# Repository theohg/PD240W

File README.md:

# PD240W

An adjustable power supply for motor drives using USB-C Power Delivery negotiation, supporting up to **240W at 48V 5A**. This device is designed to be compatible with USB-PD up to 3.2. Firmware runs on a Raspberry Pi Pico ([RP2040](https://www.raspberrypi.com/products/rp2040/)).

Follow the latest project logs and updates on <a href="https://hackaday.io/project/205084-pd240w" target="_blank" title="PD240W on Hackaday.io">
Hackaday.io 
</a>

> [!WARNING]
> **Disclaimer**: Firmware v2.0.0 includes guarded AVS/EPR negotiation, startup restore, and EPR-exit handling, but high-voltage charger interoperability still depends on the source and cable combination you test with. Validate 28V/36V/48V operation on your hardware.

## Table of Contents

- [Features](#features)
- [Hardware](#hardware)
- [Quick Start](#quick-start)
- [Controls](#controls)
- [Firmware Structure](#firmware-structure)
- [Want one?](#want-one)
- [Planned Features](#planned-features)
- [Acknowledgements](#acknowledgements)

## Features

- **USB-C Power Delivery**: Negotiates Fixed, PPS (3.3-21V programmable), and AVS (15-48V EPR) profiles
- **Current Limiting**: Adjustable 10mA-5A via INA228 power monitor with hardware overcurrent protection
- **LCD Interface**: 240x320 ST7789 display with anti-aliased fonts and Prusa-style encoder navigation
- **Safety**: Overcurrent ISR, overtemperature monitoring (NTC + INA228)
- **Settings Persistence**: User settings stored in RP2040 flash with CRC32 validation
- **Auto PPS/AVS Tuning**: Closed-loop voltage correction for PPS/AVS charger output accuracy
- **Charger Diagnostics**: On-device PD revision, charger identity, cable inference, and max-power reporting
- **Remote CLI**: USB serial command interface for measurements, PD selection, and settings updates
- **Energy Monitoring**: Tracks mAh delivered since boot via INA228 charge accumulator
- **17V Buck Output**: Optional mock STO/SBC voltage for motor drive safety circuits
- **Configurable**: Brightness, auto-dim, startup melody, auto-output on boot and more

## Hardware

| Type | Path | Contents |
|------|------|----------|
| PCB (STEP) | `3D_models/PD240W_PCB.stp` | Full PCB 3D model |
| Enclosure (STL) | `3D_models/enclosure/` | Casing top/bottom, knob, button, LCD support, SWD cover |
| Gerbers | `PCB_files/Manufacturing/Fabrication/` | PCB manufacturing files |
| BOM | `PCB_files/Manufacturing/Assembly/` | Bill of materials |
| Pick & Place | `PCB_files/Manufacturing/Assembly/` | Pick and place file |

### Hardware Erata

USB data lines (D+/D-) are reversed in the current PCB revision, preventing native USB communication between the RP2040 and the USB host. This can be easily fixed by crossing the D+ and D- lines on the PCB by crossing the series 27Ω resistors as shown below:

## Quick Start

### Flash Pre-built Firmware

1. Download `PD240W.uf2` from the [latest release](https://github.com/theohg/PD240W/releases/latest)
2. Hold **BOOTSEL** button on the Pico while connecting USB
3. Drag `PD240W.uf2` to the mounted `RPI-RP2` drive

### Build from Source

Requires: [Pico SDK 2.3.0](https://github.com/raspberrypi/pico-sdk), ARM GCC toolchain, CMake, Ninja

```bash
git clone --recurse-submodules https://github.com/theohg/PD240W.git
cd PD240W

mkdir -p build && cd build
cmake -G Ninja ..
ninja
```

The output binary is `build/PD240W.uf2`.

The INA228 driver is tracked as a Git submodule in `external/ina228_multiplatform`. If you already cloned the repository without submodules, run:

```bash
git submodule update --init --recursive
```

PD240W does not automatically follow the newest INA228 library release. The version is pinned by the parent repository's recorded submodule commit for `external/ina228_multiplatform`, and that exact checked-out commit is what gets compiled into the firmware. Prebuilt `PD240W.uf2` releases already include that pinned INA version.

### Flash via SWD

```bash
openocd -f interface/cmsis-dap.cfg -f target/rp2040.cfg \
  -c "adapter speed 5000; program build/PD240W.elf verify reset exit"
```

> [!IMPORTANT]
> **EEPROM Initial Setup**: Before full PD negotiation can work, you must flash the **TPS26750 EEPROM** configuration. This is done via the **EEPROM Flash** workflow found in the **Settings** menu. 
> 
> **Note**: Before the EEPROM is flashed, the board will only power on when connected to a standard 5V non-PD charger (USB BC1.2 mode).

Once the firmware has been successfully flashed, connect the device to a compatible USB-PD power source and interact with the encoder and buttons to navigate the menus and adjust settings as explained below.

> [!NOTE]
> Finding a compact and affordable charger supporting **USB-PD 3.1** (up to 48V EPR) is currently quite rare. Here are a few known options:
>
> | Model | Max single-port PD Output | Voltage Profile | Approx. Price |
> |---|---|---|---|
> | **[UGREEN Nexode 140W](https://fr.ugreen.com/products/ugreen-nexode-140w-chargeur-usb-c-pd-3-1-3-ports)** | 140W | 28V @ 5A | ~60€ |
> | **[Framework Power Adapter - 180W](https://frame.work/fr/fr/products/16-power-adapter?v=FRANCR000F)** | 180W | 36V @ 5A | ~109€ |
> | **[HKY 240W GaN Charger](https://www.amazon.de/-/en/Charger-Framework-Thunderbolt-External-ADP-240KB/dp/B0FLXY1HYW/ref=sr_1_2?crid=3N3IPHZQ5LLC7&dib=eyJ2IjoiMSJ9.Hby-yLg1Ti0JNivqvDzvN57zIH6zG4_c9wlyL50Z52GmOPyP_vKubcMJ3zNZ7RRcIgOo2FKgZio1hprqALfRdOTl2DQ7Dp27o4l66qmaDQw9ctSuX0EaWnDfyVwVAMaSwnUP7h1NBuraYlZnAgiljw.9cbe3P4mLf8D7-0faSCcJpKki5cfrjZLwFO-zW9XlJw&dib_tag=se&keywords=hky+240w&qid=1769454134&sprefix=hky+240w%2Caps%2C102&sr=8-2)** | 240W | 48V @ 5A | ~90€ |
> | **[Framework Power Adapter - 240W](https://frame.work/fr/fr/products/power-adapter-240w?v=FRAKMX000F)** | 240W | 48V @ 5A | ~120€ |
> | **[UGREEN NEXODE 500W](https://eu.ugreen.com/products/ugreen-nexode-500w-6-port-gan-desktop-fast-charger)** | 240W | 48V @ 5A | ~250€ |

## Controls

| Input | Action |
|-------|--------|
| Encoder Rotate | Navigate menus / Adjust values |
| Encoder Click | Confirm / Select |
| BTN1 (top) | Toggle load switch output |
| BTN2 (bottom) | Toggle 17V buck (requires VBUS > 18V) |

### Menu Structure

```mermaid
graph TD
  %% Nodes
      Boot([Boot]) -->|≤2s| Main[Main Screen]
      Main -->|Error| Fault[Fault Screen]
      Fault -->|Click| Main
      
      Main <-->|Click| Menu[Main Menu]

      Menu --> Voltage[Select Voltage]
      Menu --> Current[Current Limit]
      Menu --> Settings[Settings]
      Menu --> AboutFirmware[About PD240W]
      Menu --> AboutCharger[About This Charger]
      Menu --> Back[Back]

      Voltage <-->|Select PDO| AdjV[Adjust Voltage]
      Current <-->|Set Limit| AdjC[Adjust Current]
      
      Settings --> EEPROM[Flash EEPROM]
      Settings --> Configs[Params: Brightness / Sounds / Tuning...]
      AboutFirmware --> Main
      AboutCharger --> Main
      
      %% Styling
      classDef default fill:#f9f9f9,stroke:#333,stroke-width:1px;
      classDef alert fill:#ffcccc,stroke:#cc0000,stroke-width:2px;
      class Fault alert;
```

| Menu Item | Description |
|-----------|-------------|
| Select Voltage | Fixed / PPS / AVS PDO selection |
| Current Limit | 10mA - 5A output current limit adjustment with encoder acceleration |
| Settings | EEPROM flash workflow plus tuning, startup, brightness, and sound options |
| About PD240W | Device identity, firmware build info, flash usage, and project link |
| About This Charger | Live PD revision, CC orientation, QC inference, and cable diagnostics |
| Back | Return to the main live display |

## Firmware Structure

```
src/
├── main.cpp                        Entry point, non-blocking main event loop
├── hardware.h/cpp                  Hardware singleton aggregating all drivers
├── interrupts.h/cpp                Centralized GPIO interrupt router (RP2040 single-callback)
│
├── config/
│   ├── board_config.h              Pin definitions (Board:: namespace)
│   ├── app_config.h                Timeouts, thresholds, limits (AppConfig:: namespace)
│   └── version.h                   Firmware & hardware version, author...
│
├── drivers/                        Low-level hardware drivers (no business logic)
│   ├── display/
│   │   ├── st7789.h/cpp            SPI LCD driver with AA font rendering
│   │   ├── aa_font.h               Anti-aliased font data structure
│   │   └── font_inter_*.h          Generated Inter font bitmaps (14/20/28px)
│   ├── power/
│   │   └── tps26750/               USB-PD controller: PDO discovery, contract negotiation
│   ├── input/
│   │   ├── rotary_enc.h/cpp        Quadrature encoder with velocity tracking
│   │   ├── button.h/cpp            Debounced button with click/long-press
│   │   └── adc_inputs.h/cpp        VBUS voltage + NTC temperature (ADC channels)
│   ├── gpio/                       SimpleIO: digital output with non-blocking blink
│   ├── buzzer/                     PWM buzzer with melody playback
│   └── rgb_led/                    SK6812 via PIO state machine
│
├── logic/                          Application logic
│   ├── state_machine.h/cpp         BOOT -> MAIN <-> MENU <-> ADJUST, FAULT handling
│   ├── safety.h/cpp                Temperature/voltage/current monitoring, fault triggers
│   ├── pd_manager.h/cpp            PD contract caching, PPS keep-alive, auto-tuning
│   ├── settings.h/cpp              Flash persistence with CRC32, debounced saves
│   └── tps_eeprom_workflow.h/cpp   TPS26750 EEPROM compare/flash state machine
│
├── ui/
│   ├── display_manager.h/cpp       All screen rendering (boot, main, menu, adjust, fault)
│   ├── font_config.h               Central font size mapping (FONT_LARGE/MEDIUM/SMALL)
│   └── assets/synapticon_logo.h    Boot screen logo bitmap
│
├── utils/
│   ├── logging.h                   LOG_INFO/WARN/ERROR/DEBUG/CRITICAL macros
│   ├── pd_voltage.h                Shared programmable-voltage alignment helper
│   ├── tps_eeprom_loader.h/cpp     Low-level TPS26750 EEPROM read/write
│   └── tps26750_patch.c            TPS26750 binary configuration blob
```

## Want one?

Feel free to order assembled PCBs, flash the firmware, and test it for yourself! Manufacturing 5 assembled PCBs will cost approximately **$415**. 

The project is open for contributions. Don't hesitate to improve the code, report bugs, or suggest new features via Pull Requests and Issues!

## License and Copyright

This repository contains different types of source files, which are licensed as follows:

### 1. Hardware files (CC BY-NC 4.0)
All hardware design files in the PCB_files directory (Schematics, PCB layout, Gerbers, BOM) and 3D printable enclosure files are licensed under the **Creative Commons Attribution-NonCommercial 4.0 International License**. 

You are free to download, modify, and build this board for personal, educational, and hobbyist use. However, you may **not** use these designs for commercial purposes (such as manufacturing and selling the boards) without prior written permission.

Please see the [LICENSE.txt](./LICENSE.txt) file for full terms.

### 2. Firmware & Software (MIT License)
The firmware and software source code in this repository is licensed under the **MIT License**. 

You are free to use, modify, and distribute the software component of this project. 

Please see the [LICENSE-FIRMWARE.txt](./LICENSE-FIRMWARE.txt) file for full terms.

## Planned Features for V2.1.0+

- **PPS battery charging in Constant Current (CC) mode**: PPS allows a fixed current mode that can be used for battery charging. This is to be tested by charging lithium-ion battery packs.
- **Improved CLI interface**: Needs more testing and polish.
- **Extended PPS and AVS Range**: Support for PPS voltages as low as 3.5V, AND SPR AVS profiles down to 9V.

## Acknowledgements

This project was made possible by [Synapticon GmbH](https://www.synapticon.com), who funded and supported its development. Thank you for providing the resources, hardware, and opportunity to bring PD240W to life.

Inspiration for this project was taken from the great work on portable USB-C PD power supplies by CentyLab on the [PocketPD](https://hackaday.io/project/194295-pocketpd-usb-c-portable-bench-power-supply) project and Alex Xia with his [ProtoV MINI](https://hackaday.io/project/204461-protov-mini-tiny-usb-c-breadboard-power-supply).

All work done on this project, from Hardware design to Firmware development, was done by me, as the sole contributor. I am grateful for the support and feedback from the community, and I hope this project can be a useful resource for anyone interested in USB-C PD power supplies!

***

Made with ❤️ by Théo Heng

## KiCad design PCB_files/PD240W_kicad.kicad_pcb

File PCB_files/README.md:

<h1 align="center">PD240W</h1>

***

<p align="center">
  
&nbsp; &nbsp; &nbsp; &nbsp;
  
</p>

***

## SPECIFICATIONS

| Parameter | Value | 
| --- | --- |
| Dimensions | 66.0 × 66.0 mm |
| Input Voltage | 5 - 53 V |
| Output Voltage | 3.3 - 48 V |
| Max. Output Current Voltage | 5 A |
| Max Power Output | 240 W |

***

## DIRECTORY STRUCTURE
```
  ├─ Images             # Pictures, renders, and annotated PCB images
  ├─ lib                # KiCad footprint and symbol libraries
  │  ├─ lib_fp          # Footprint libraries
  │  └─ lib_sym         # Symbol libraries
  ├─ Logos              # Project logos used in the PCB design package
  ├─ Manufacturing      # Assembly and fabrication deliverables
  │  ├─ Assembly        # BoM, placement, and assembly notes
  │  └─ Fabrication     # Fabrication exports and release bundles
  ├─ Schematic          # Exported schematic documentation
  └─ Templates          # KiCad title block templates
```

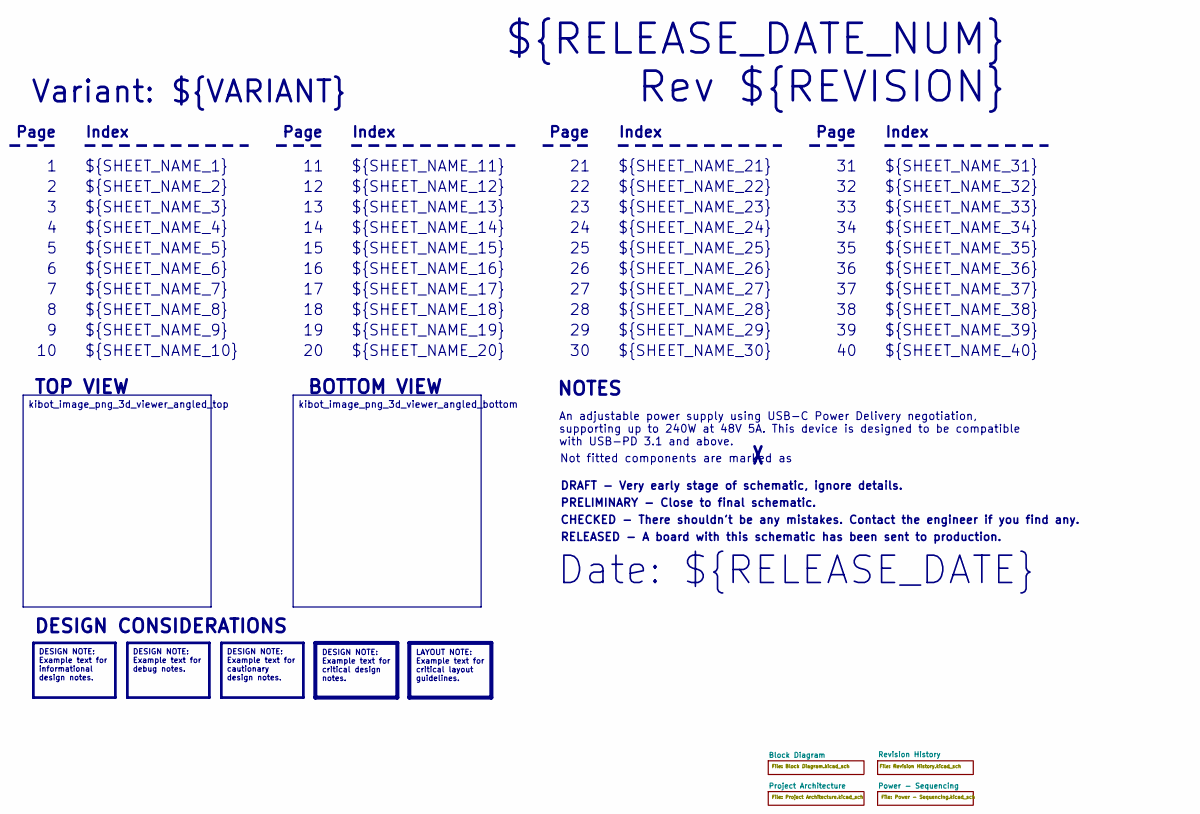
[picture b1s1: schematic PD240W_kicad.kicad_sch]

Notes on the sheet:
Variant: ${VARIANT}
RELEASED - A board with this schematic has been sent to production.
${SHEET_NAME_24}
Index
Page
PRELIMINARY - Close to final schematic.
${SHEET_NAME_22}
DRAFT - Very early stage of schematic, ignore details.
${SHEET_NAME_12}
${SHEET_NAME_8}
${SHEET_NAME_2}
${SHEET_NAME_5}
${SHEET_NAME_20}
${SHEET_NAME_23}
${RELEASE_DATE_NUM}
${SHEET_NAME_35}
Not fitted components are marked as
${SHEET_NAME_11}
${SHEET_NAME_6}
${SHEET_NAME_37}
${SHEET_NAME_26}
${SHEET_NAME_36}
Rev ${REVISION}
${SHEET_NAME_15}
CHECKED - There shouldn't be any mistakes. Contact the engineer if you find any.
BOTTOM VIEW
${SHEET_NAME_14}
${SHEET_NAME_21}
${SHEET_NAME_17}
${SHEET_NAME_18}
Date: ${RELEASE_DATE}
${SHEET_NAME_7}
${SHEET_NAME_31}
NOTES
${SHEET_NAME_40}
${SHEET_NAME_39}
${SHEET_NAME_32}
${SHEET_NAME_1}
${SHEET_NAME_9}
${SHEET_NAME_38}

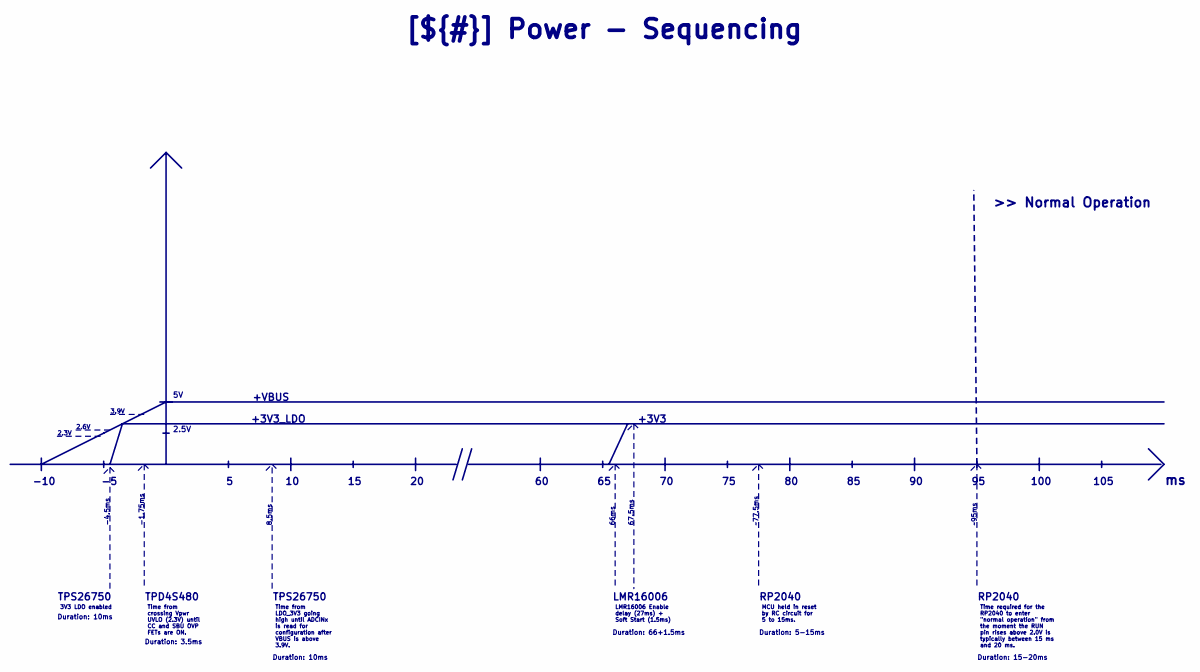
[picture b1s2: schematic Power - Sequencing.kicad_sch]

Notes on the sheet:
~95ms
-1.75ms
2.5V
3.9V
Duration: 15-20ms
RP2040
TPS26750
LMR16006
2.6V
+VBUS
Duration: 10ms
100
Duration: 3.5ms
Duration: 66+1.5ms
8.5ms
+3V3_LDO
66ms
67.5ms
Duration: 5-15ms
2.3V
105
~77.5ms
TPD4S480
+3V3
>> Normal Operation
-4.5ms
-10
3V3 LDO enabled
Time from LDO_3V3 going high until ADCINx is read for configuration after VBUS is above 3.9V.
Time from crossing Vpwr UVLO (2.3V) until CC and SBU OVP FETs are ON.
Time required for the RP2040 to enter "normal operation" from the moment the RUN pin rises above 2.0V is typically between 15 ms and 20 ms.
[${#}] ${TITLE}
MCU held in reset by RC circuit for 5 to 15ms.
LMR16006 Enable delay (27ms) + Soft Start (1.5ms)

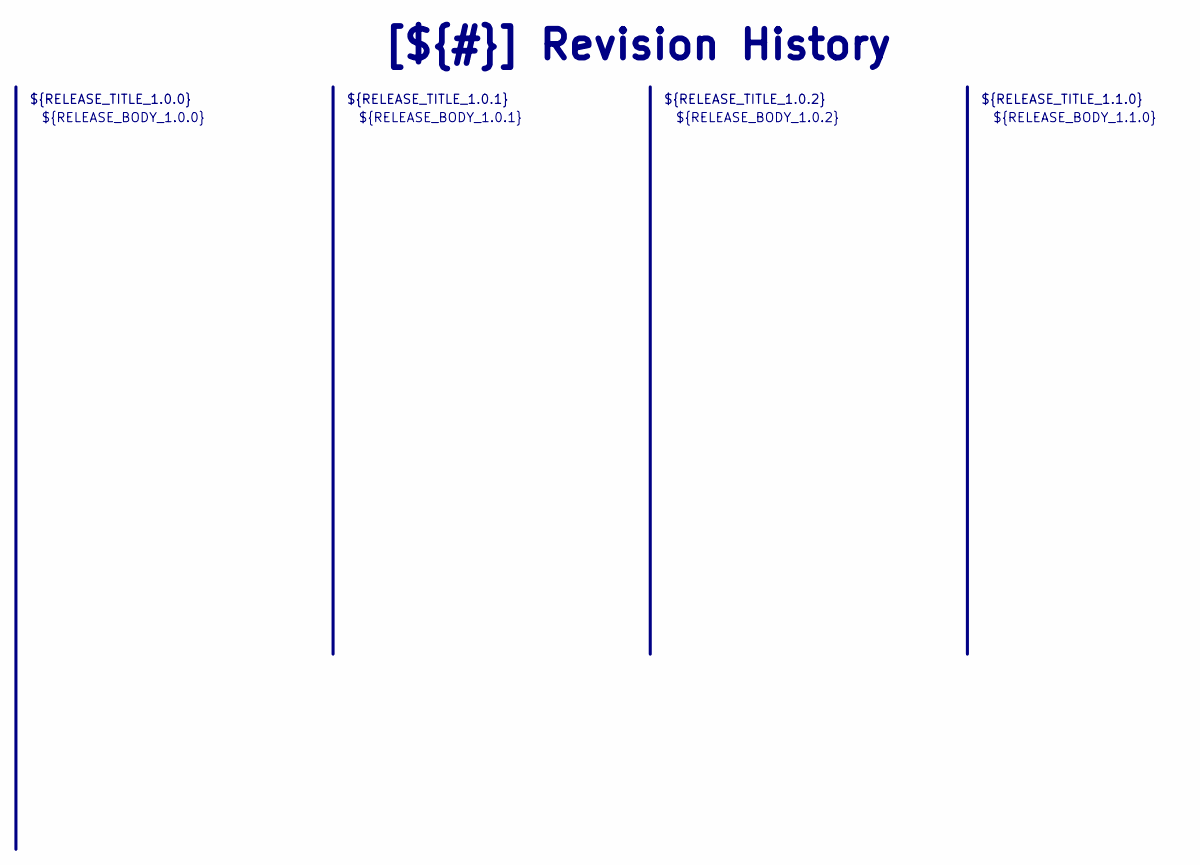
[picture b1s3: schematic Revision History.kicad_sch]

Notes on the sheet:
${RELEASE_BODY_1.1.0}
[${#}] ${TITLE}
${RELEASE_BODY_1.0.0}
${RELEASE_TITLE_1.0.2}
${RELEASE_BODY_1.0.2}
${RELEASE_BODY_1.0.1}
${RELEASE_TITLE_1.0.0}
${RELEASE_TITLE_1.0.1}
${RELEASE_TITLE_1.1.0}

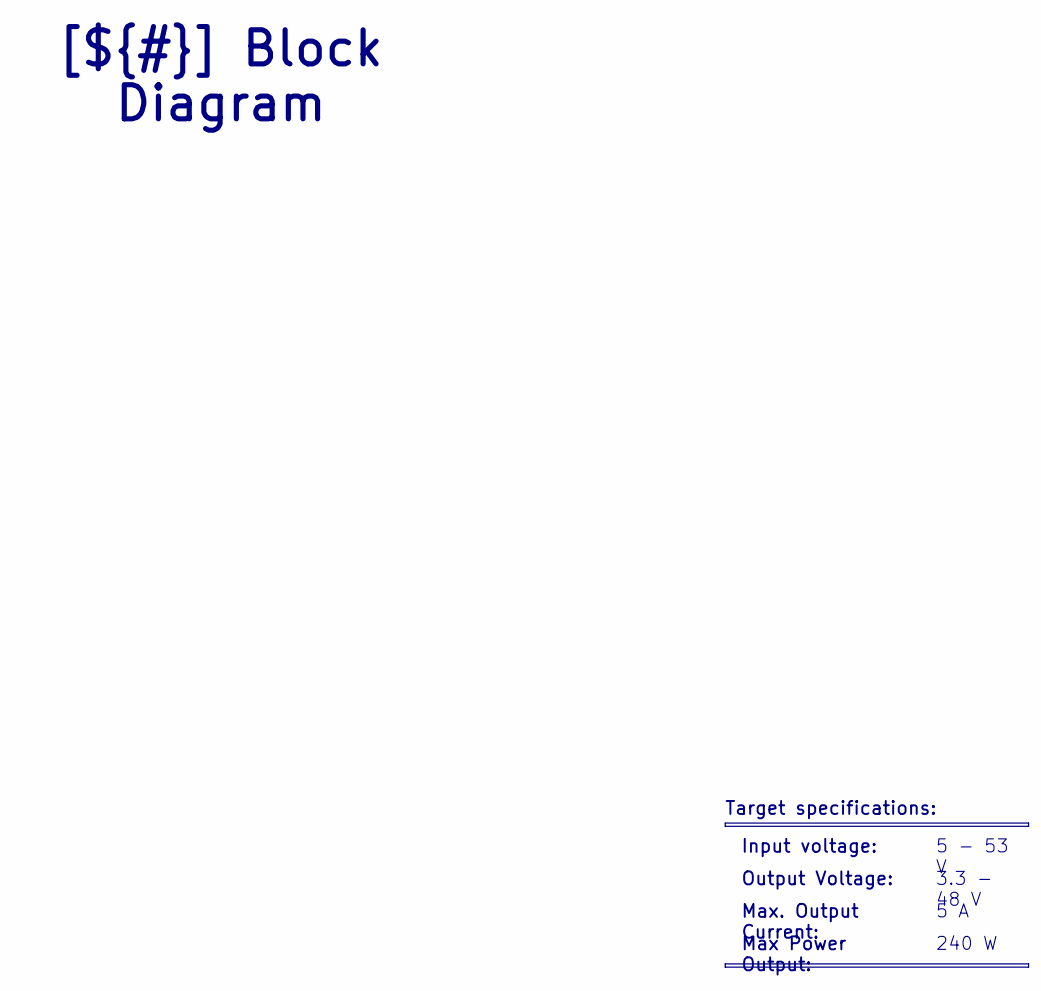
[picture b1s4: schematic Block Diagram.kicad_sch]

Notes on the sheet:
Max Power Output:
5 - 53 V
240 W
[${#}] ${TITLE}
3.3 - 48 V
Input voltage:
Target specifications:
Max. Output Current:
5 A
Output Voltage:

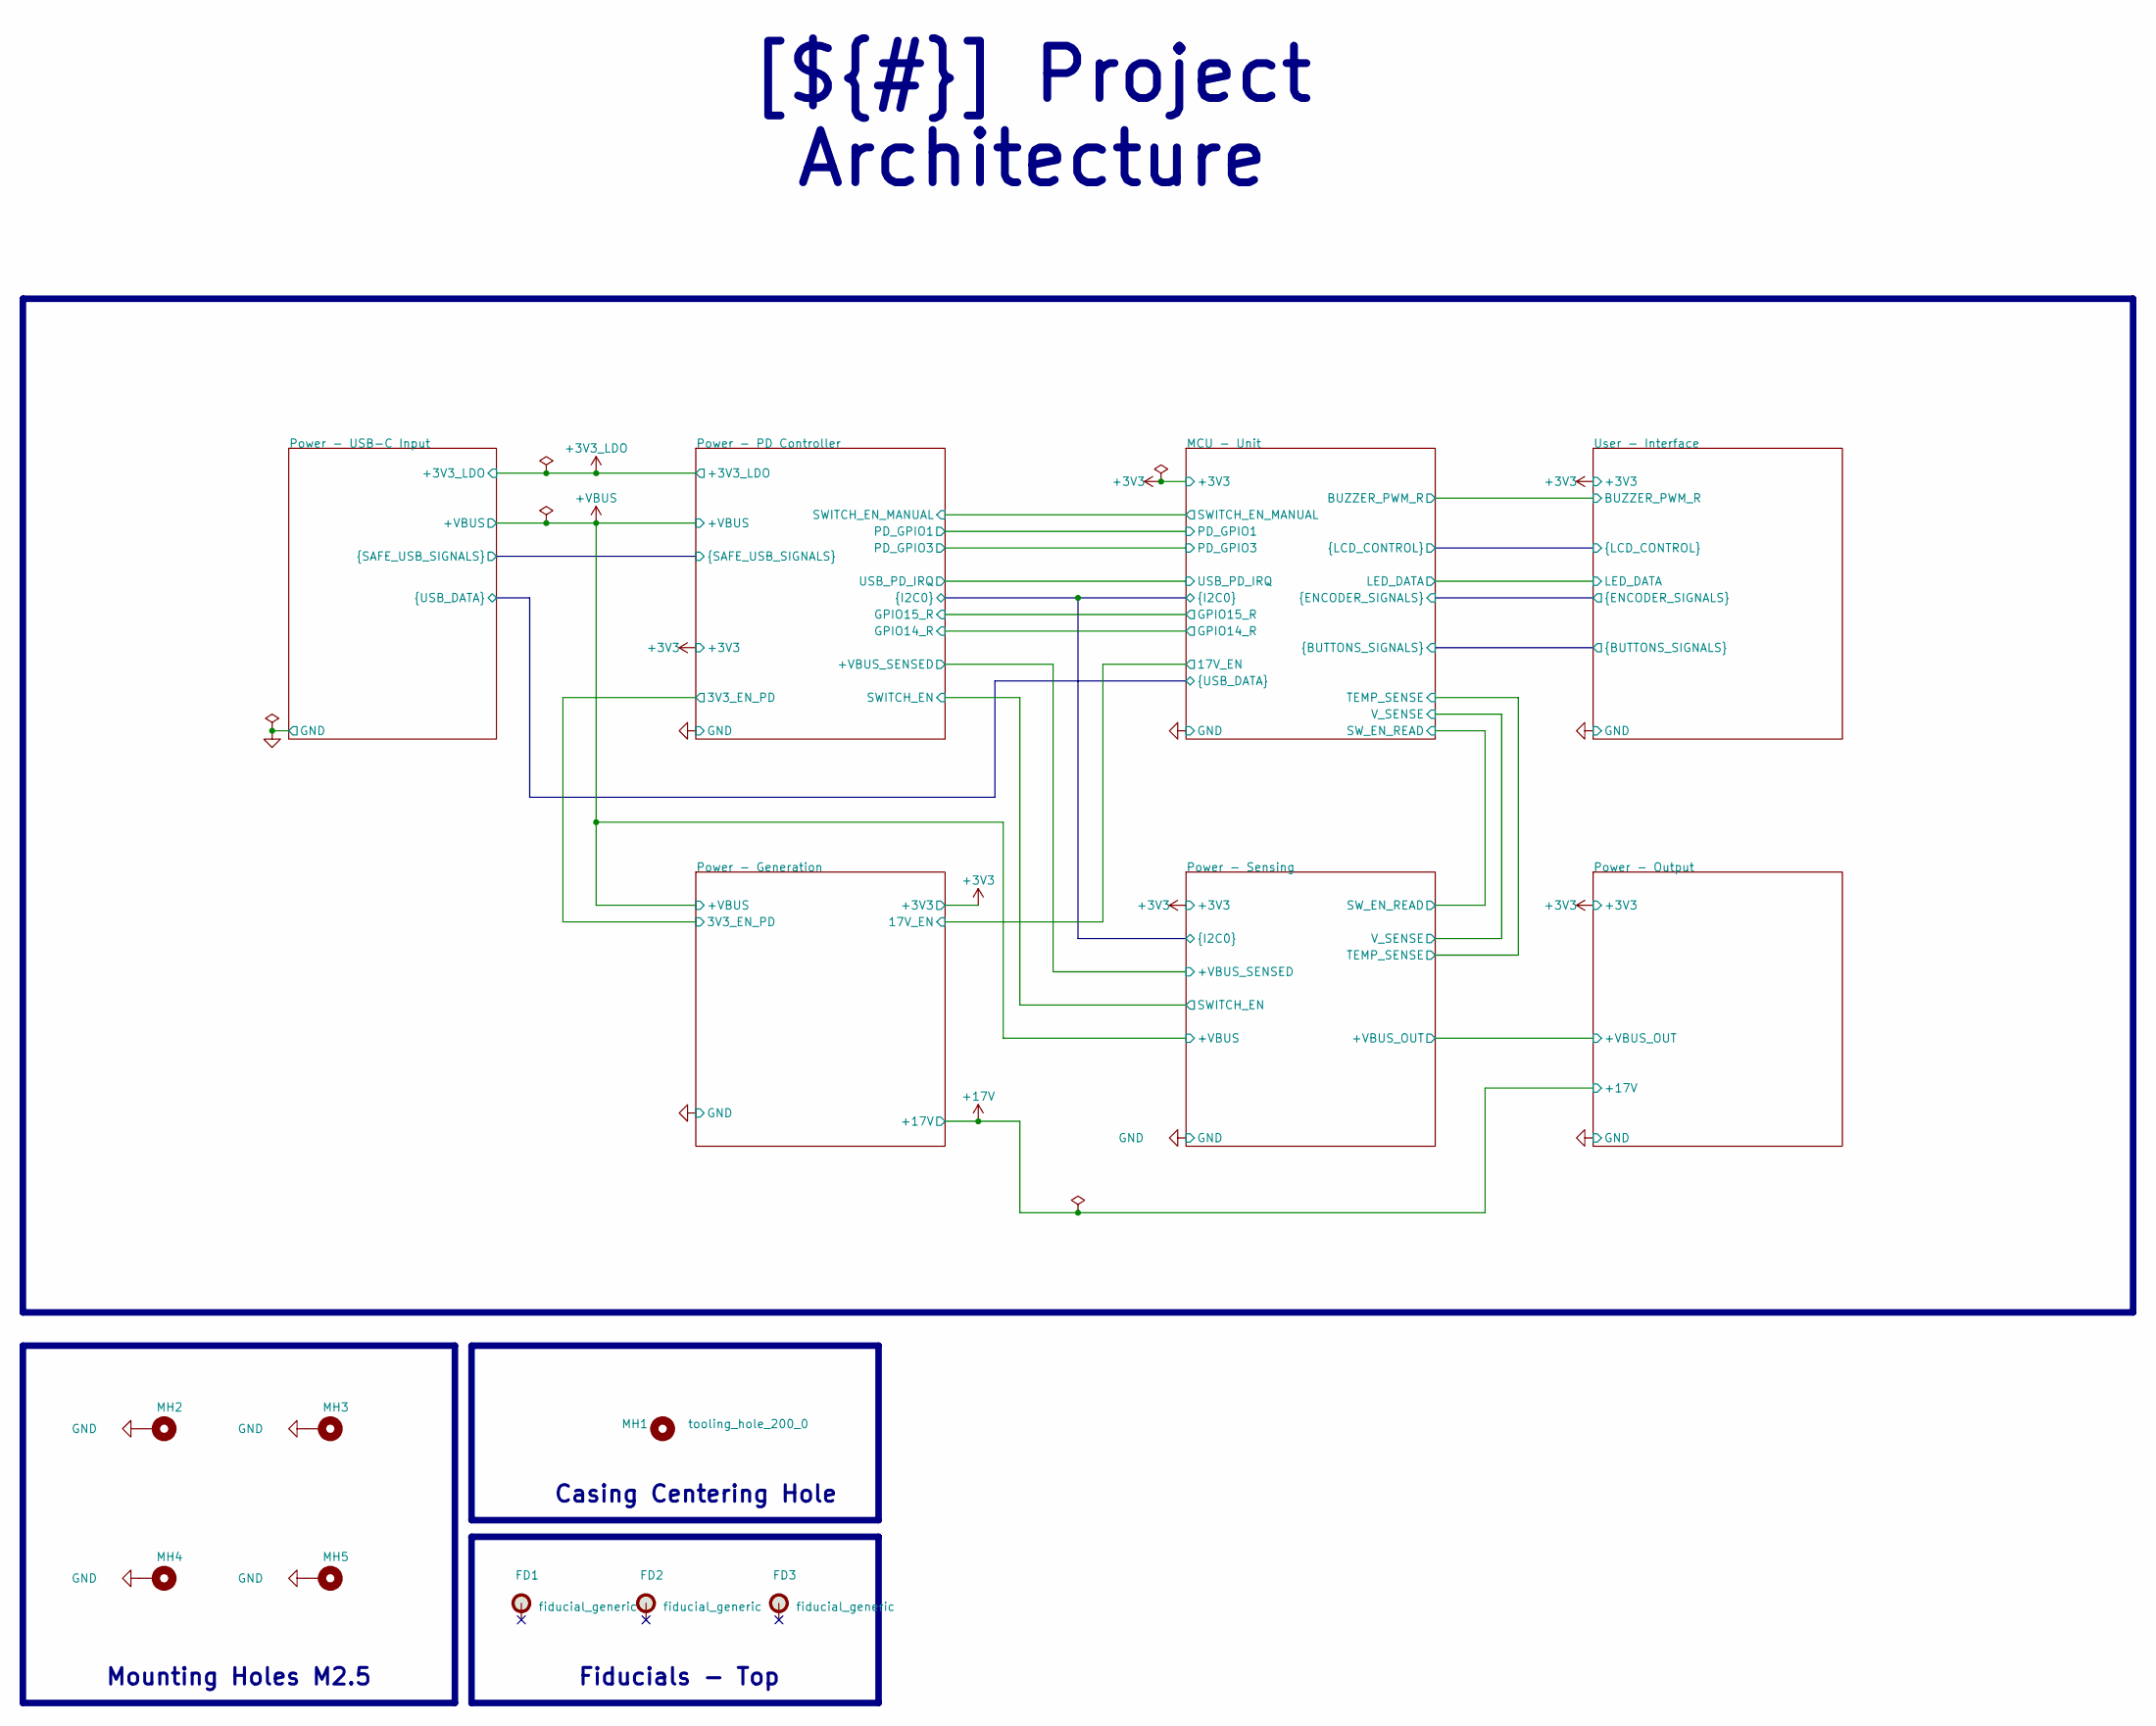
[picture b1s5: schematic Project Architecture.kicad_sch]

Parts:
FD1, FD2, FD3: fiducial_generic; fiducial_round_130
MH1: tooling_hole_200_0; tooling_hole_200_0_np
MH2, MH3, MH4, MH5: mounting_hole_270_540_p_via_8_50; MountingHole_2.7mm_M2.5_Pad_Via

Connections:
GND: MH2.1, MH3.1, MH4.1, MH5.1; also elsewhere on the board

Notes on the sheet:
Mounting Holes M2.5
Casing Centering Hole
Fiducials - Top
[${#}] ${TITLE}

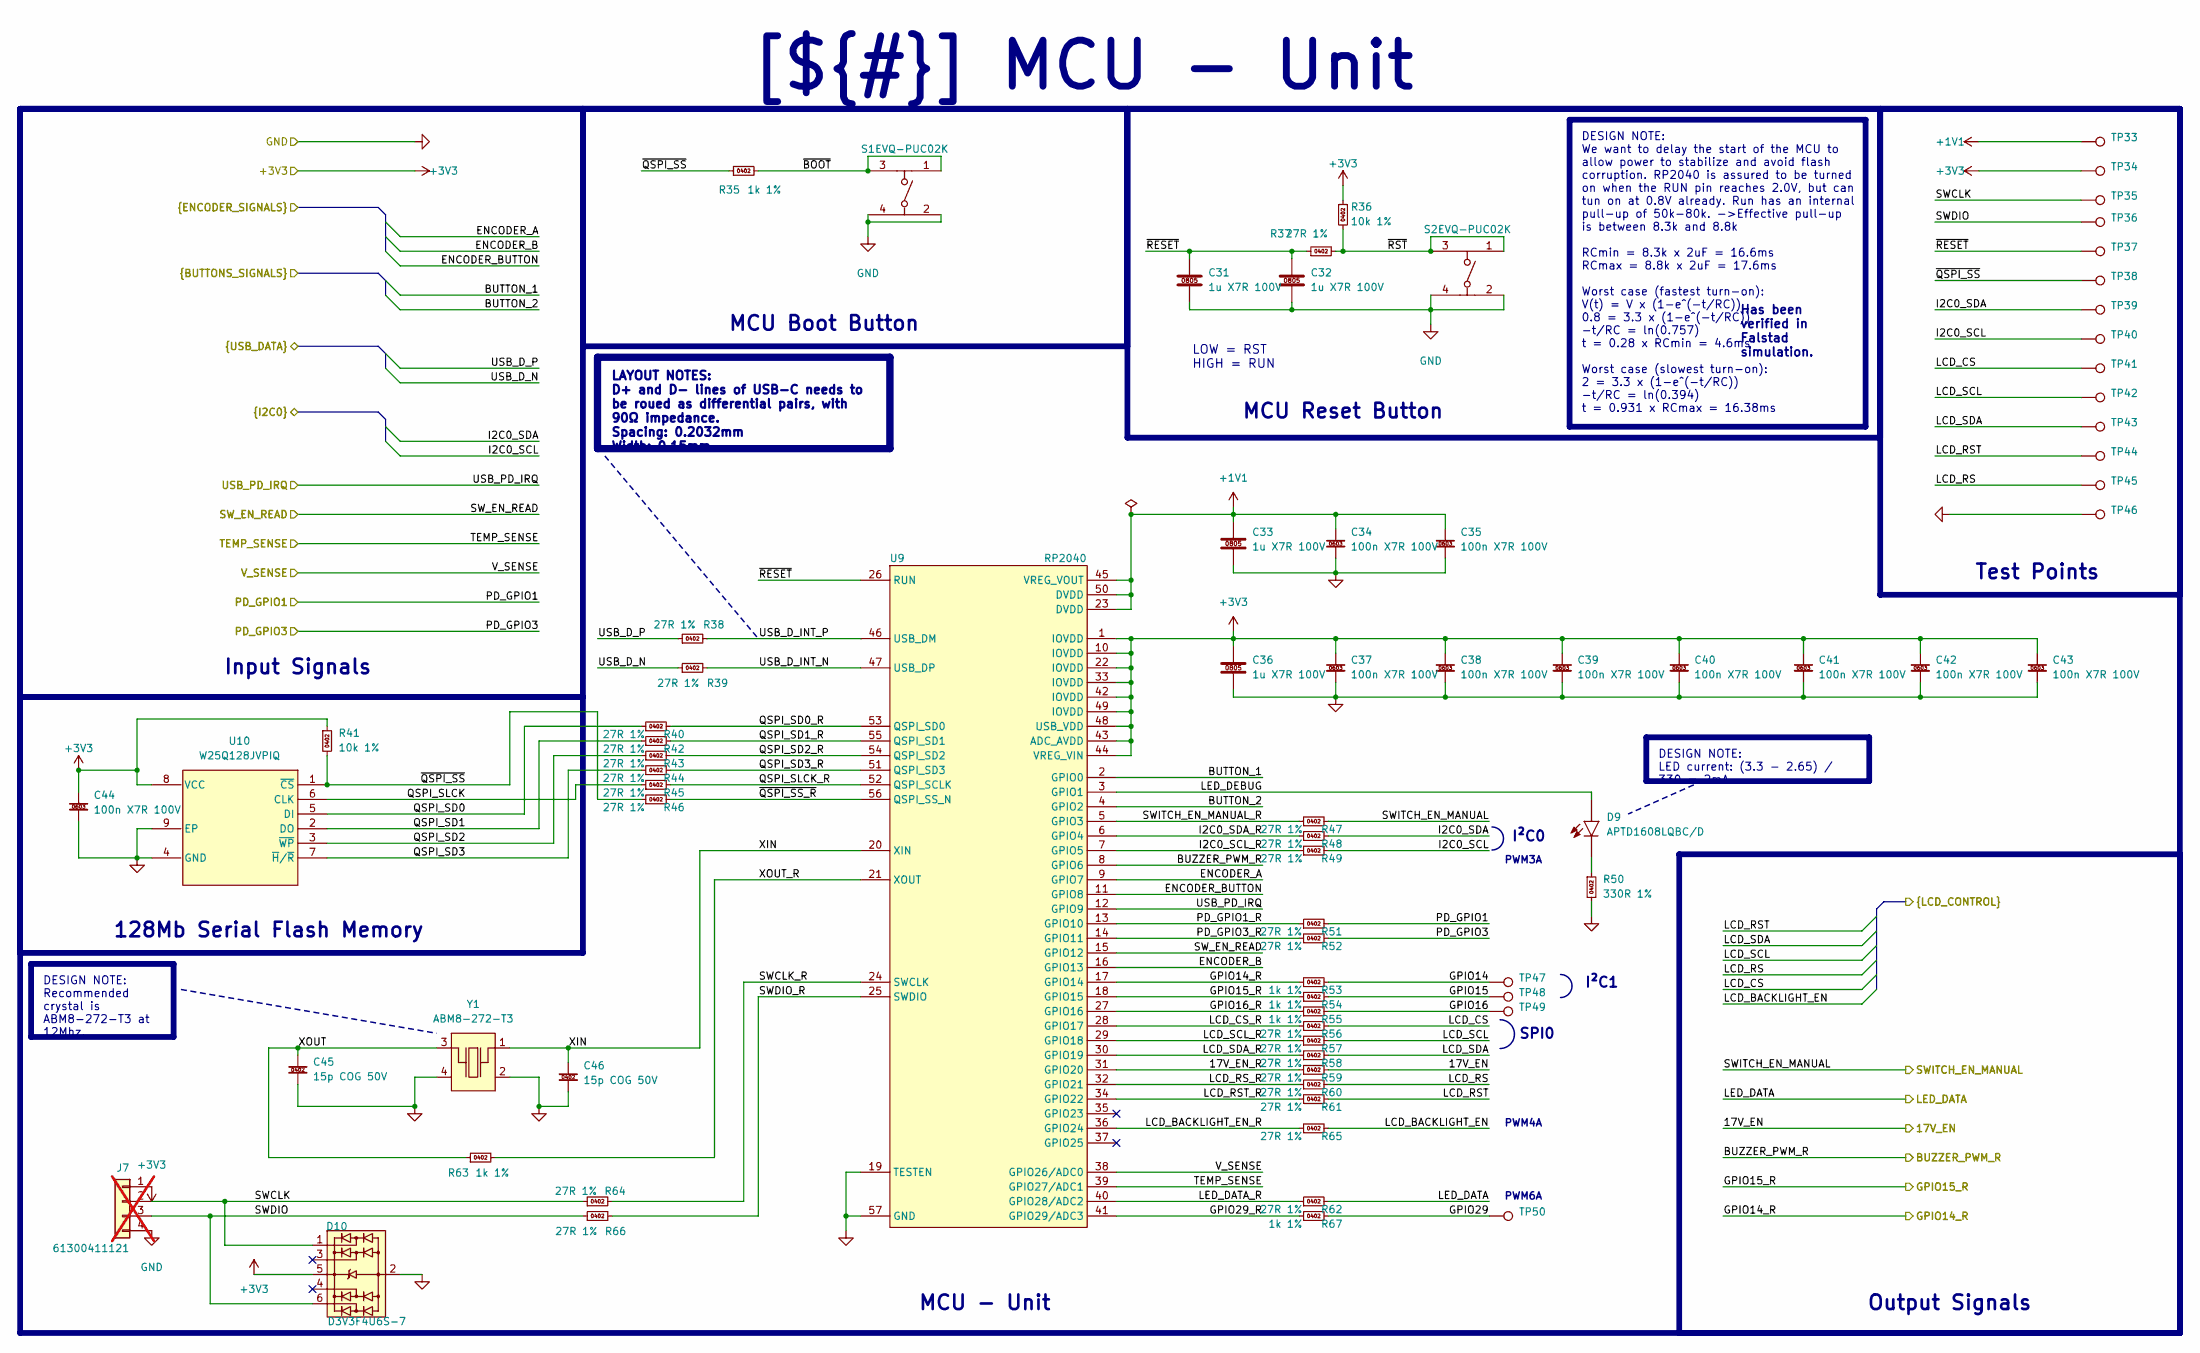
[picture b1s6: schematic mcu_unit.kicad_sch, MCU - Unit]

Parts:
C31, C32, C33, C36: 1u X7R 100V; capc_2012_14_n; Manufacturer Part Number CC0805KKX7R0BB105; LCSC C5370002
C34, C35, C37, C38, C39, C40, C41, C42, C43, C44: 100n X7R 100V; capc_1608_09_l; Manufacturer Part Number CL10B104KC8NNNC; LCSC C15725
C45, C46: 15p COG 50V; capc_1005_06_n; Manufacturer Part Number 0402CG150J500NT; LCSC C1548
D9: APTD1608LQBC/D; kingbright_0603_blue; Manufacturer Part Number APTD1608LQBC/D; LCSC C5344742
D10: D3V3F4U6S-7; sot363_sc88_65p_200x125x110_n; Manufacturer Part Number D3V3F4U6S-7; LCSC C1869321
J7: 61300411121; we_61300411121; Manufacturer Part Number 61300411121; LCSC C5184785; not fitted
R35, R53, R54, R55, R63, R67: 1k 1%; resc_1005_04_m; Manufacturer Part Number 0402WGF1001TCE; LCSC C11702
R36, R41: 10k 1%; resc_1005_04_n; Manufacturer Part Number 0402WGF1002TCE; LCSC C25744
R37, R38, R39, R40, R42, R43, R44, R45, R46, R47, R48, R49, R51, R52, R56, R57, R58, R59, R60, R61, R62, R64, R65, R66: 27R 1%; resc_1005_04_m; Manufacturer Part Number RC0402FR-0727RL; LCSC C138021
R50: 330R 1%; resc_1005_04_m; Manufacturer Part Number 0402WGF3300TCE; LCSC C25104
S1, S2: EVQ-PUC02K; EVQPUC02K; Manufacturer Part Number EVQ-PUC02K; LCSC C79174
TP33, TP34, TP35, TP36, TP37, TP38, TP39, TP40, TP41, TP42, TP43, TP44, TP45: tp_round_70
TP46, TP47, TP48, TP49, TP50: sp_oval_300x100
U9: RP2040; qfn56_40p_700x700x90_tp_320x320_mfg; Manufacturer Part Number SC0914(13); LCSC C2040
U10: W25Q128JVPIQ; wson8_127p_600x500x80_tp_435x340_n; Manufacturer Part Number W25Q128JVPIQ; LCSC C190862
Y1: ABM8-272-T3; osccc_320x205x80_abm8; Manufacturer Part Number ABM8-272-T3; LCSC C20625731

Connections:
+1V1: C33.1, C34.1, C35.1, TP33.1, U9.23 (DVDD), U9.45 (VREG_VOUT), U9.50 (DVDD)
+3V3: C36.1, C37.1, C38.1, C39.1, C40.1, C41.1, C42.1, C43.1, C44.1, D10.5, J7.1, R36.1, R41.1, TP34.1, U9.1 (IOVDD), U9.10 (IOVDD), U9.22 (IOVDD), U9.33 (IOVDD), U9.42 (IOVDD), U9.43 (ADC_AVDD), U9.44 (VREG_VIN), U9.48 (USB_VDD), U9.49 (IOVDD), U10.8 (VCC); also elsewhere on the board
/Project Architecture/MCU - Unit/17V_EN: R59.2; also elsewhere on the board
/Project Architecture/MCU - Unit/17V_EN_R: R59.1, U9.31 (GPIO20)
/Project Architecture/MCU - Unit/BUTTON_1: U9.2 (GPIO0); also elsewhere on the board
/Project Architecture/MCU - Unit/BUTTON_2: U9.4 (GPIO2); also elsewhere on the board
/Project Architecture/MCU - Unit/BUZZER_PWM_R: U9.8 (GPIO6); also elsewhere on the board
/Project Architecture/MCU - Unit/ENCODER_A: U9.9 (GPIO7); also elsewhere on the board
/Project Architecture/MCU - Unit/ENCODER_B: U9.16 (GPIO13); also elsewhere on the board
/Project Architecture/MCU - Unit/ENCODER_BUTTON: U9.11 (GPIO8); also elsewhere on the board
/Project Architecture/MCU - Unit/GPIO14: R53.2, TP47.1
/Project Architecture/MCU - Unit/GPIO14_R: R53.1, U9.17 (GPIO14); also elsewhere on the board
/Project Architecture/MCU - Unit/GPIO15: R54.2, TP48.1
/Project Architecture/MCU - Unit/GPIO15_R: R54.1, U9.18 (GPIO15); also elsewhere on the board
/Project Architecture/MCU - Unit/GPIO16: R55.2, TP49.1
/Project Architecture/MCU - Unit/GPIO16_R: R55.1, U9.27 (GPIO16)
/Project Architecture/MCU - Unit/GPIO29: R67.2, TP50.1
/Project Architecture/MCU - Unit/GPIO29_R: R67.1, U9.41 (GPIO29/ADC3)
/Project Architecture/MCU - Unit/I2C0_SCL: R49.2, TP40.1; also elsewhere on the board
/Project Architecture/MCU - Unit/I2C0_SCL_R: R49.1, U9.7 (GPIO5)
/Project Architecture/MCU - Unit/I2C0_SDA: R48.2, TP39.1; also elsewhere on the board
/Project Architecture/MCU - Unit/I2C0_SDA_R: R48.1, U9.6 (GPIO4)
/Project Architecture/MCU - Unit/LCD_BACKLIGHT_EN: R65.2; also elsewhere on the board
/Project Architecture/MCU - Unit/LCD_BACKLIGHT_EN_R: R65.1, U9.36 (GPIO24)
/Project Architecture/MCU - Unit/LCD_CS: R56.2, TP41.1; also elsewhere on the board
/Project Architecture/MCU - Unit/LCD_CS_R: R56.1, U9.28 (GPIO17)
/Project Architecture/MCU - Unit/LCD_RS: R60.2, TP45.1; also elsewhere on the board
/Project Architecture/MCU - Unit/LCD_RST: R61.2, TP44.1; also elsewhere on the board
/Project Architecture/MCU - Unit/LCD_RST_R: R61.1, U9.34 (GPIO22)
/Project Architecture/MCU - Unit/LCD_RS_R: R60.1, U9.32 (GPIO21)
/Project Architecture/MCU - Unit/LCD_SCL: R57.2, TP42.1; also elsewhere on the board
/Project Architecture/MCU - Unit/LCD_SCL_R: R57.1, U9.29 (GPIO18)
/Project Architecture/MCU - Unit/LCD_SDA: R58.2, TP43.1; also elsewhere on the board
/Project Architecture/MCU - Unit/LCD_SDA_R: R58.1, U9.30 (GPIO19)
/Project Architecture/MCU - Unit/LED_DATA: R62.2; also elsewhere on the board
/Project Architecture/MCU - Unit/LED_DATA_R: R62.1, U9.40 (GPIO28/ADC2)
/Project Architecture/MCU - Unit/LED_DEBUG: D9.2 (A), U9.3 (GPIO1)
/Project Architecture/MCU - Unit/PD_GPIO1: R51.2; also elsewhere on the board
/Project Architecture/MCU - Unit/PD_GPIO1_R: R51.1, U9.13 (GPIO10)
/Project Architecture/MCU - Unit/PD_GPIO3: R52.2; also elsewhere on the board
/Project Architecture/MCU - Unit/PD_GPIO3_R: R52.1, U9.14 (GPIO11)
/Project Architecture/MCU - Unit/QSPI_SD0: R40.1, U10.5 (DI)
/Project Architecture/MCU - Unit/QSPI_SD0_R: R40.2, U9.53 (QSPI_SD0)
/Project Architecture/MCU - Unit/QSPI_SD1: R42.1, U10.2 (DO)
/Project Architecture/MCU - Unit/QSPI_SD1_R: R42.2, U9.55 (QSPI_SD1)
/Project Architecture/MCU - Unit/QSPI_SD2: R43.1, U10.3 (~WP)
/Project Architecture/MCU - Unit/QSPI_SD2_R: R43.2, U9.54 (QSPI_SD2)
/Project Architecture/MCU - Unit/QSPI_SD3: R44.1, U10.7 (~H/~R)
/Project Architecture/MCU - Unit/QSPI_SD3_R: R44.2, U9.51 (QSPI_SD3)
/Project Architecture/MCU - Unit/QSPI_SLCK: R45.1, U10.6 (CLK)
/Project Architecture/MCU - Unit/QSPI_SLCK_R: R45.2, U9.52 (QSPI_SCLK)
/Project Architecture/MCU - Unit/SWCLK: D10.1, J7.2, R64.1, TP35.1
/Project Architecture/MCU - Unit/SWCLK_R: R64.2, U9.24 (SWCLK)
/Project Architecture/MCU - Unit/SWDIO: D10.6, J7.3, R66.1, TP36.1
/Project Architecture/MCU - Unit/SWDIO_R: R66.2, U9.25 (SWDIO)
/Project Architecture/MCU - Unit/SWITCH_EN_MANUAL: R47.2; also elsewhere on the board
/Project Architecture/MCU - Unit/SWITCH_EN_MANUAL_R: R47.1, U9.5 (GPIO3)
/Project Architecture/MCU - Unit/SW_EN_READ: U9.15 (GPIO12); also elsewhere on the board
/Project Architecture/MCU - Unit/TEMP_SENSE: U9.39 (GPIO27/ADC1); also elsewhere on the board
/Project Architecture/MCU - Unit/USB_D_INT_N: R39.2, U9.47 (USB_DP)
/Project Architecture/MCU - Unit/USB_D_INT_P: R38.2, U9.46 (USB_DM)
/Project Architecture/MCU - Unit/USB_D_N: R39.1; also elsewhere on the board
/Project Architecture/MCU - Unit/USB_D_P: R38.1; also elsewhere on the board
/Project Architecture/MCU - Unit/USB_PD_IRQ: U9.12 (GPIO9); also elsewhere on the board
/Project Architecture/MCU - Unit/V_SENSE: U9.38 (GPIO26/ADC0); also elsewhere on the board
/Project Architecture/MCU - Unit/XIN: C46.1, U9.20 (XIN), Y1.1
/Project Architecture/MCU - Unit/XOUT: C45.1, R63.1, Y1.3
/Project Architecture/MCU - Unit/XOUT_R: R63.2, U9.21 (XOUT)
/Project Architecture/MCU - Unit/~BOOT: R35.2, S1.1, S1.3
/Project Architecture/MCU - Unit/~QSPI_SS_R: R46.2, U9.56 (QSPI_SS_N)
/Project Architecture/MCU - Unit/~QSPI_SS: R35.1, R41.2, R46.1, TP38.1, U10.1 (~CS)
/Project Architecture/MCU - Unit/~RESET: C31.1, C32.1, R37.1, TP37.1, U9.26 (RUN)
/Project Architecture/MCU - Unit/~RST: R36.2, R37.2, S2.1, S2.3
GND: C31.2, C32.2, C33.2, C34.2, C35.2, C36.2, C37.2, C38.2, C39.2, C40.2, C41.2, C42.2, C43.2, C44.2, C45.2, C46.2, D10.2, J7.4, R50.2, S1.2, S1.4, S2.2, S2.4, TP46.1, U9.19 (TESTEN), U9.57 (GND), U10.4 (GND), U10.9 (EP), Y1.2, Y1.4; also elsewhere on the board
unnamed: D9.1 (C), R50.1

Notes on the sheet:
PWM4A
MCU Boot Button
MCU Reset Button
Input Signals
128Mb Serial Flash Memory
Test Points
I²C1
Output Signals
SPI0
I²C0
PWM6A
${TITLE}
PWM3A
LOW = RST HIGH = RUN
LAYOUT NOTES: D+ and D- lines of USB-C needs to be roued as differential pairs, with 90Ω impedance. Spacing: 0.2032mm Width: 0.15mm
DESIGN NOTE: We want to delay the start of the MCU to allow power to stabilize and avoid flash corruption. RP2040 is assured to be turned on when the RUN pin reaches 2.0V, but can tun on at 0.8V already. Run has an internal pull-up of 50k-80k. ->Effective pull-up is between 8.3k and 8.8k RCmin = 8.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
DESIGN NOTE: Recommended crystal is ABM8-272-T3 at 12Mhz.
Has been verified in Falstad simulation.
DESIGN NOTE: LED current: (3.3 - 2.65) / 330 = 2mA
[${#}] ${TITLE}
